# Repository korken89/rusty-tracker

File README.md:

# Rusty Tracker

**A learning board for LTE-M and tracking technologies**

## Versions

There are 2 versions of the board, based on:

1. uBlox R422-M10S
2. nRF9160 + uBlox M10S GNSS

which can be found in the `master` branch and `nrf` branch respectively.

The two IFA antennas are simulated with Ansys HFSS, files are available.

### uBlox R422-M10S version

This is the main board that development is happening for in the `firmware` folder.

The hardware is tested and working.

### nRF9160 version

This was made as well for learning, not manufactured nor tested.

## License

This work is licensed under [CERN-OHL-P](cern_ohl_p_v2.txt).

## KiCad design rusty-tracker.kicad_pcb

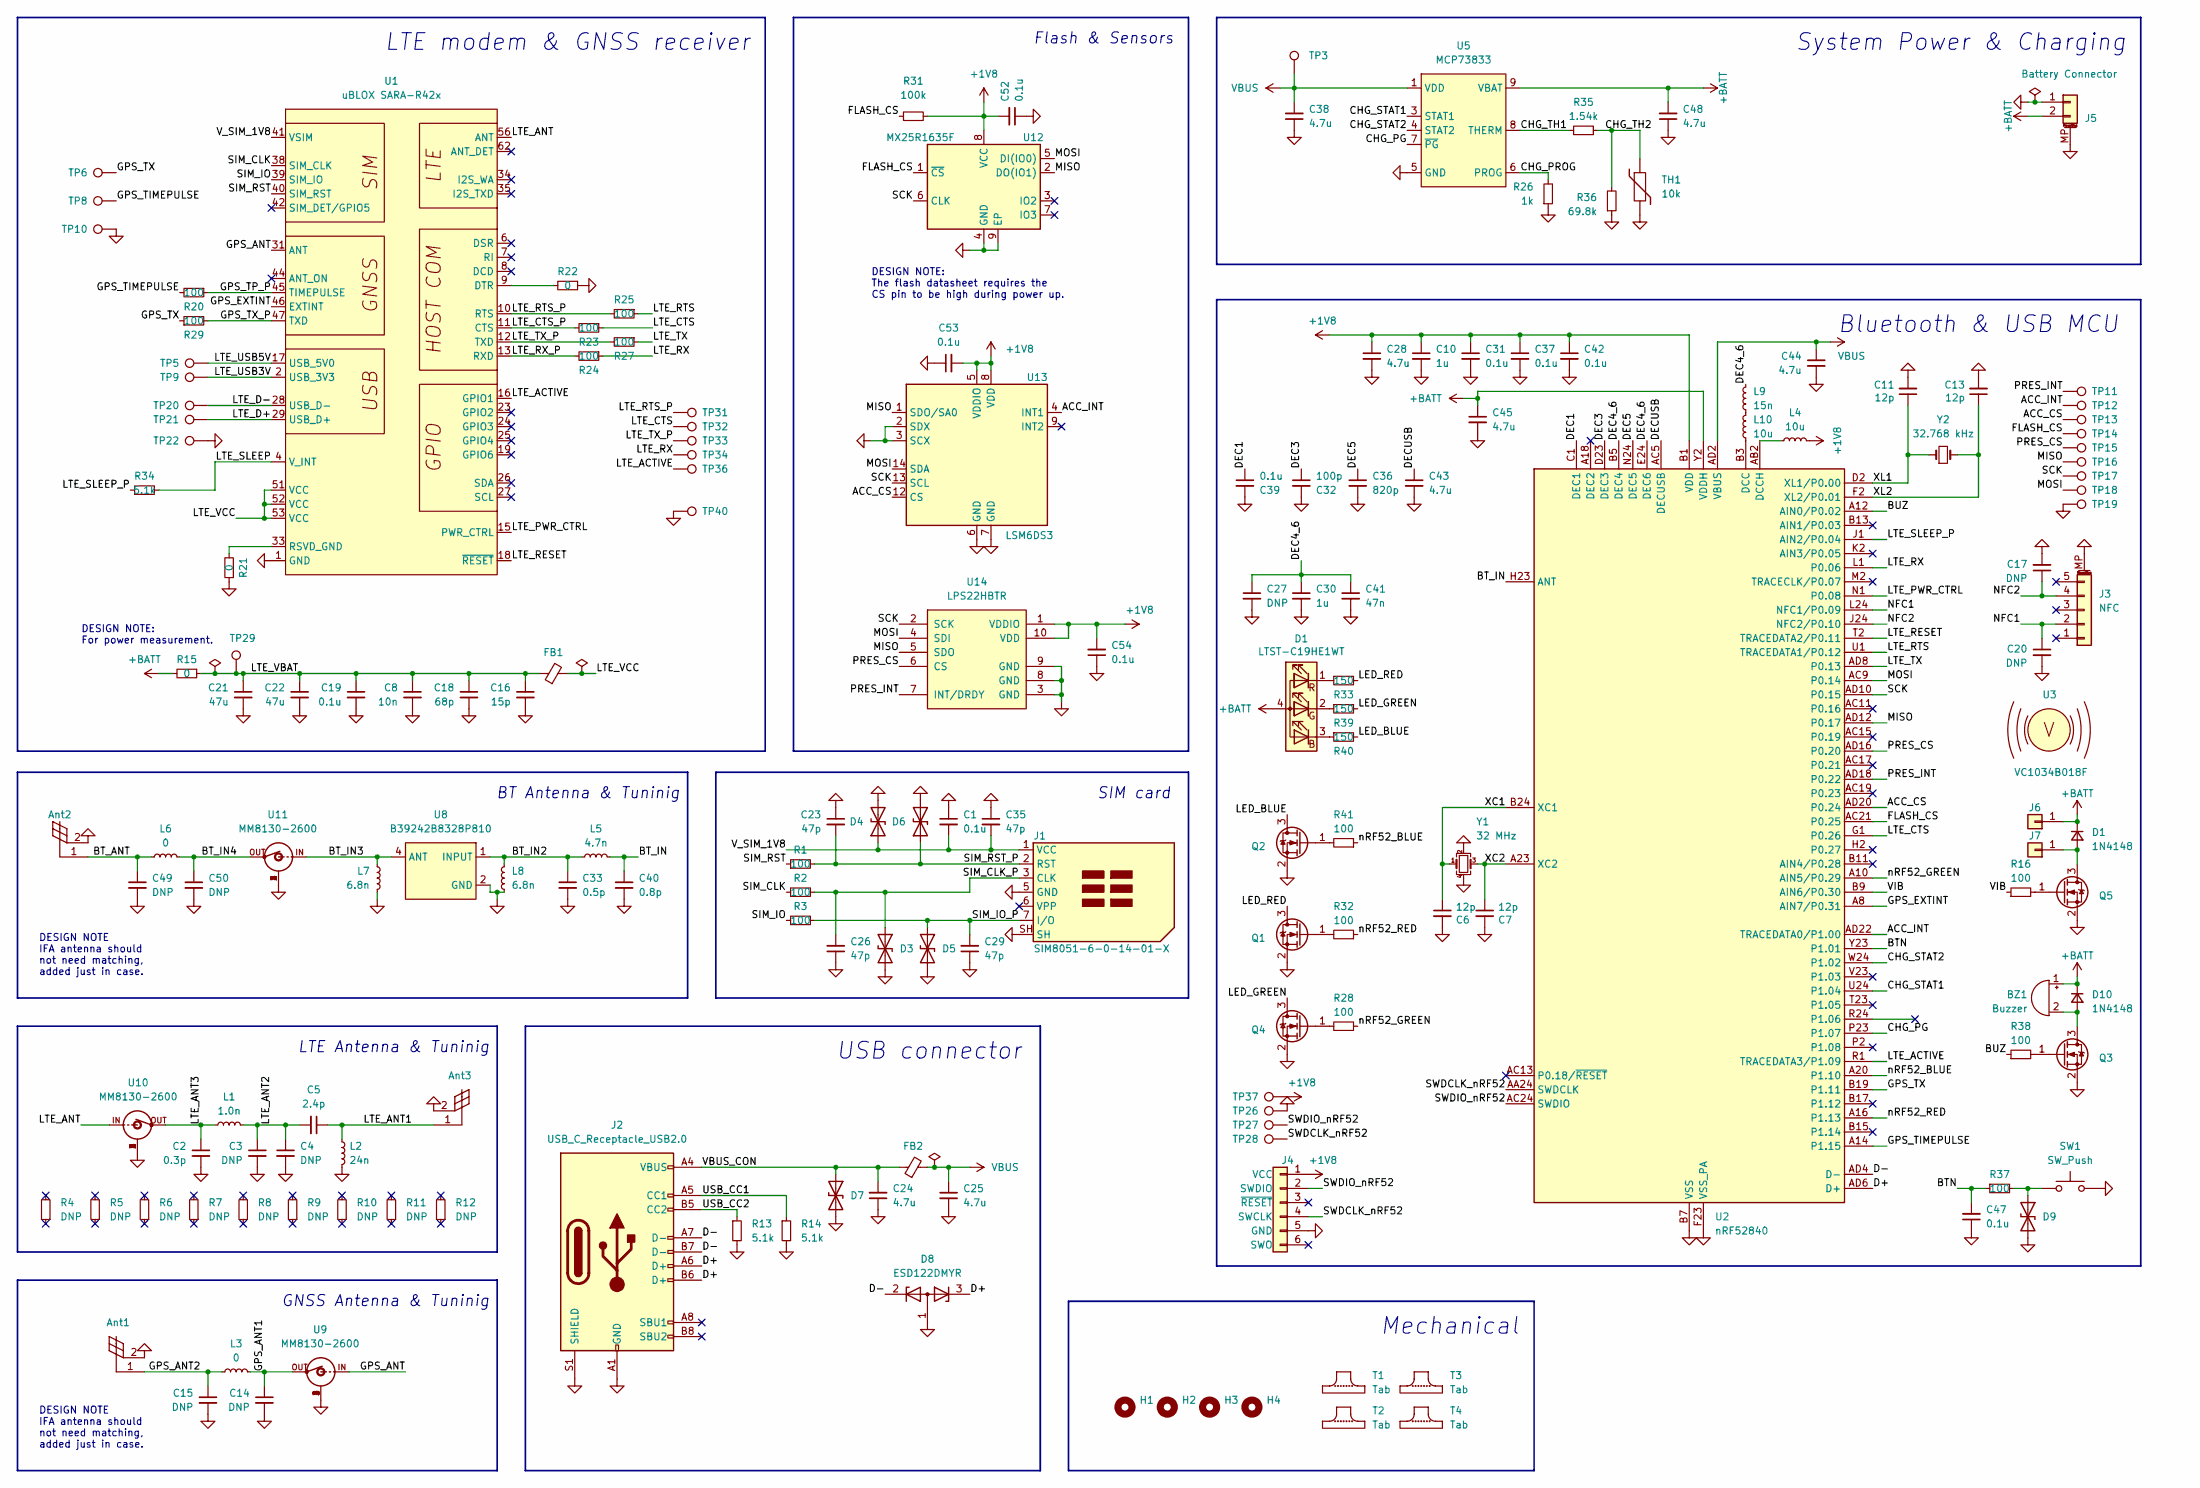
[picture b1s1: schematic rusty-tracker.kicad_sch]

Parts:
Ant1: antenna; gps-inverted-f
Ant2: antenna; 2.4ghz-inverted-f
Ant3: antenna; P822602
BZ1: Buzzer; AST0927
C1, C19, C31, C37, C39, C42, C47, C52, C53, C54: 0.1u; C_0402
C2: 0.3p; C_0402
C3, C4, C17, C20, C27: DNP; C_0402
C5: 2.4p; C_0402
C6, C7: 12p; C_0402; Tolerance 1%
C8: 10n; C_0402
C10, C30: 1u; C_0402
C11, C13: 12p; C_0402
C14, C15, C49, C50: DNP; C_0201
C16: 15p; C_0402
C18: 68p; C_0402
C21, C22: 47u; C_0805
C23, C26, C29, C35: 47p; C_0402
C24, C25, C28, C38, C43, C44, C45, C48: 4.7u; C_0402
C32: 100p; C_0402
C33: 0.5p; C_0201
C36: 820p; C_0402
C40: 0.8p; C_0201
C41: 47n; C_0402
D1, D10: 1N4148; D_0402_DFN1006
D3, D4, D5, D6, D7, D9: D_TVS; D_0402_DFN1006
D8: ESD122DMYR; X2SON
FB1, FB2: BLM18EG221SN1D; R_0603
H1, H2, H3, H4: MountingHole_Pad; MountingHole_2.2mm_M2
J1: SIM8051-6-0-14-01-X
J2: USB_C_Receptacle_USB2.0; USB_C_Receptacle_USB4105
J3: NFC; TE_0-1734839-5_1x05-1MP_P0.5mm_Horizontal
J4: tag-connect-swd; Tag-Connect_TC2030-IDC-NL_2x03_P1.27mm_Vertical
J5: Battery Connector; JST_SH_SM02B-SRSS-TB_1x02-1MP_P1.00mm_Horizontal
J6, J7: Conn_01x01; pad_circ_1.5mm
L1: 1.0n; R_0402
L2: 24n; R_0402
L3, L6: 0; R_0201
L4, L10: 10u; R_0603
L5: 4.7n; R_0201
L7, L8: 6.8n; R_0201
L9: 15n; R_0402
Q1, Q2, Q3, Q4, Q5: RUM002N02T2L; SOT-723
R1, R2, R3, R16, R20, R23, R24, R25, R27, R28, R29, R32, R37, R38, R41: 100; R_0402
R4, R5, R6, R7, R8, R9, R10, R11, R12: DNP; ANT_0402
R13, R14, R34: 5.1k; R_0402
R15, R21, R22: 0; R_0402
R26: 1k; R_0402
R31: 100k; R_0402
R33, R39, R40: 150; R_0402
R35: 1.54k; R_0402
R36: 69.8k; R_0402
SW1: SW_Push; SW_SPST_EVQP2
T1, T2, T3, T4: Tab
TH1: 10k; R_0402
TP3, TP5, TP6, TP8, TP9, TP10, TP11, TP12, TP13, TP14, TP15, TP16, TP17, TP18, TP19, TP20, TP21, TP22, TP26, TP27, TP28, TP29, TP31, TP32, TP33, TP34, TP36, TP37, TP40: TestPoint; TestPoint_Pad_D1.0mm
U1: uBLOX SARA-R42x; u-blox SARA-R4
U2: nRF52840; Nordic_AQFN-73-1EP_7x7mm_P0.5mm
U3: VC1034B018F
U5: MCP73833; DFN-10-1EP_3x3mm_P0.5mm_EP1.55x2.48mm
U8: B39242B8328P810
U9, U10, U11: MM8130-2600
U12: MX25R1635F; USON-8-3x2mm-EP
U13: LSM6DS3; LGA-14_3x2.5mm_P0.5mm_LayoutBorder3x4y
U14: LPS22HBTR; ST_HLGA-10_2x2mm_P0.5mm_LayoutBorder3x2y
Y1: 32 MHz; Crystal_4Pin_2.0x1.6mm
Y2: 32.768 kHz; Crystal_SMD_2012-2Pin_2.0x1.2mm

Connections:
+1V8: C10.1, C28.1, C31.1, C37.1, C42.1, C52.2, C53.2, C54.2, J4.1 (VCC), L4.1, R31.2, TP37.1, U2.A22 (VDD), U2.AD14 (VDD), U2.AD23 (VDD), U2.B1 (VDD), U2.W1 (VDD), U12.8 (VCC), U13.5 (VDDIO), U13.8 (VDD), U14.1 (VDDIO), U14.10 (VDD)
/ACC_CS: TP13.1, U2.AD20 (P0.24), U13.12 (CS)
/ACC_INT: TP12.1, U2.AD22 (TRACEDATA0/P1.00), U13.4 (INT1)
/BTN: C47.2, R37.1, U2.Y23 (P1.01)
/BT_ANT: Ant2.1, C49.1, L6.2
/BT_IN: C40.1, L5.1, U2.H23 (ANT)
/BT_IN2: C33.1, L5.2, L8.1, U8.1 (INPUT)
/BT_IN3: L7.2, U8.4 (ANT), U11.IN
/BT_IN4: C50.1, L6.1, U11.OUT
/BUZ: R38.1, U2.A12 (AIN0/P0.02)
/CHG_PG: U2.P23 (P1.07), U5.7 (~PG)
/CHG_PROG: R26.2, U5.6 (PROG)
/CHG_STAT1: U2.U24 (P1.04), U5.3 (STAT1)
/CHG_STAT2: U2.W24 (P1.02), U5.4 (STAT2)
/CHG_TH1: R35.2, U5.8 (THERM)
/CHG_TH2: R35.1, R36.2, TH1.1
/D+: D8.3 (K), J2.A6 (D+), J2.B6 (D+), U2.AD6 (D+)
/D-: D8.2 (K), J2.A7 (D-), J2.B7 (D-), U2.AD4 (D-)
/DEC1: C39.1, U2.C1 (DEC1)
/DEC3: C32.1, U2.D23 (DEC3)
/DEC4_6: C27.1, C30.1, C41.1, L9.1, U2.B5 (DEC4), U2.E24 (DEC6)
/DEC5: C36.1, U2.N24 (DEC5)
/DECUSB: C43.1, U2.AC5 (DECUSB)
/FLASH_CS: R31.1, TP14.1, U2.AC21 (P0.25), U12.1 (~CS)
/GPS_ANT: U1.31 (ANT), U9.IN
/GPS_ANT1: C14.1, L3.2, U9.OUT
/GPS_ANT2: Ant1.1, C15.1, L3.1
/GPS_EXTINT: U1.46 (EXTINT), U2.A8 (AIN7/P0.31)
/GPS_TIMEPULSE: R20.2, TP8.1, U2.A14 (P1.15)
/GPS_TP_P: R20.1, U1.45 (TIMEPULSE)
/GPS_TX: R29.1, TP6.1, U2.B19 (P1.11)
/GPS_TX_P: R29.2, U1.47 (TXD)
/LED_BLUE: Q2.3 (D), R40.2
/LED_GREEN: Q4.3 (D), R39.2
/LED_RED: Q1.3 (D), R33.2
/LTE_ACTIVE: TP36.1, U1.16 (GPIO1), U2.R1 (TRACEDATA3/P1.09)
/LTE_ANT: U1.56 (ANT), U10.IN
/LTE_ANT1: Ant3.1, C5.1, L2.1
/LTE_ANT2: C3.1, C4.1, C5.2, L1.2
/LTE_ANT3: C2.1, L1.1, U10.OUT
/LTE_CTS: R23.1, TP32.1, U2.G1 (P0.26)
/LTE_CTS_P: R23.2, U1.11 (CTS)
/LTE_D+: TP21.1, U1.29 (USB_D+)
/LTE_D-: TP20.1, U1.28 (USB_D-)
/LTE_PWR_CTRL: U1.15 (PWR_CTRL), U2.N1 (P0.08)
/LTE_RESET: U1.18 (~RESET), U2.T2 (TRACEDATA2/P0.11)
/LTE_RTS: R25.1, U2.U1 (TRACEDATA1/P0.12)
/LTE_RTS_P: R25.2, TP31.1, U1.10 (RTS)
/LTE_RX: R24.1, TP34.1, U2.L1 (P0.06)
/LTE_RX_P: R24.2, U1.13 (RXD)
/LTE_SLEEP: R34.2, U1.4 (V_INT)
/LTE_SLEEP_P: R34.1, U2.J1 (AIN2/P0.04)
/LTE_TX: R27.1, U2.AD8 (P0.13)
/LTE_TX_P: R27.2, TP33.1, U1.12 (TXD)
/LTE_USB3V: TP9.1, U1.2 (USB_3V3)
/LTE_USB5V: TP5.1, U1.17 (USB_5V0)
/LTE_VBAT: C8.1, C16.1, C18.1, C19.1, C21.1, C22.1, FB1.1, R15.1, TP29.1
/LTE_VCC: FB1.2, U1.51 (VCC), U1.52 (VCC), U1.53 (VCC)
/MISO: TP16.1, U2.AD12 (P0.17), U12.2 (DO(IO1)), U13.1 (SDO/SA0), U14.5 (SDO)
/MOSI: TP18.1, U2.AC9 (P0.14), U12.5 (DI(IO0)), U13.14 (SDA), U14.4 (SDI)
/NFC1: C20.1, J3.2, U2.L24 (NFC1/P0.09)
/NFC2: C17.1, J3.4, U2.J24 (NFC2/P0.10)
/PRES_CS: TP15.1, U2.AD16 (P0.20), U14.6 (CS)
/PRES_INT: TP11.1, U2.AD18 (P0.22), U14.7 (INT/DRDY)
/SCK: TP17.1, U2.AD10 (P0.15), U12.6 (CLK), U13.13 (SCL), U14.2 (SCK)
/SIM_CLK: R2.1, U1.38 (SIM_CLK)
/SIM_CLK_P: C26.2, D3.1 (A1), J1.3 (CLK), R2.2
/SIM_IO: R3.1, U1.39 (SIM_IO)
/SIM_IO_P: C29.2, D5.1 (A1), J1.7 (I/O), R3.2
/SIM_RST: R1.1, U1.40 (SIM_RST)
/SIM_RST_P: C23.2, D6.1 (A1), J1.2 (RST), R1.2
/SWDCLK_nRF52: J4.4 (SWCLK), TP28.1, U2.AA24 (SWDCLK)
/SWDIO_nRF52: J4.2 (SWDIO), TP27.1, U2.AC24 (SWDIO)
/USB_CC1: J2.A5 (CC1), R14.1
/USB_CC2: J2.B5 (CC2), R13.1
/VBUS_CON: C24.2, D7.1 (A1), FB2.1, J2.A4 (VBUS), J2.A9 (VBUS), J2.B4 (VBUS), J2.B9 (VBUS)
/VIB: R16.1, U2.B9 (AIN6/P0.30)
/V_SIM_1V8: C1.2, C35.2, D4.1 (A1), J1.1 (VCC), U1.41 (VSIM)
/XC1: C6.1, U2.B24 (XC1), Y1.1
/XC2: C7.1, U2.A23 (XC2), Y1.3
/XL1: C11.1, U2.D2 (XL1/P0.00), Y2.1
/XL2: C13.1, U2.F2 (XL2/P0.01), Y2.2
/nRF52_BLUE: R41.1, U2.A20 (P1.10)
/nRF52_GREEN: R28.1, U2.A10 (AIN5/P0.29)
/nRF52_RED: R32.1, U2.A16 (P1.13)
GND: Ant1.2, Ant2.2, Ant3.2, C1.1, C2.2, C3.2, C4.2, C6.2, C7.2, C8.2, C10.2, C11.2, C13.2, C14.2, C15.2, C16.2, C17.2, C18.2, C19.2, C20.2, C21.2, C22.2, C23.1, C24.1, C25.2, C26.1, C27.2, C28.2, C29.1, C30.2, C31.2, C32.2, C33.2, C35.1, C36.2, C37.2, C38.1, C39.2, C40.2, C41.2, C42.2, C43.2, C44.2, C45.2, C47.1, C48.1, C49.2, C50.2, C52.1, C53.1, C54.1, D3.2 (A2), D4.2 (A2), D5.2 (A2), D6.2 (A2), D7.2 (A2), D8.1 (A), D9.2 (A2), J1.5 (GND), J1.SH, J2.A1 (GND), J2.A12 (GND), J2.B1 (GND), J2.B12 (GND), J2.S1 (SHIELD), J3.MP (MountPin), J4.5 (GND), J5.1, J5.MP (MountPin), L2.2, L7.1, L8.2, Q1.2 (S), Q2.2 (S), Q3.2 (S), Q4.2 (S), Q5.2 (S), R13.2, R14.2, R21.1, R22.1, R26.1, R36.1, SW1.2, TH1.2, TP10.1, TP19.1, TP22.1, TP26.1, TP40.1, U1.1 (GND), U1.3 (GND), U1.5 (GND), U1.14 (GND), U1.20 (GND), U1.21 (GND), U1.22 (GND), U1.30 (GND), U1.32 (GND), U1.43 (GND), U1.50 (GND), U1.54 (GND), U1.55 (GND), U1.57 (GND), U1.58 (GND), U1.59 (GND), U1.60 (GND), U1.61 (GND), U1.63 (GND), U1.64 (GND), U1.65 (GND), U1.66 (GND), U1.67 (GND), U1.68 (GND), U1.69 (GND), U1.70 (GND), U1.71 (GND), U1.72 (GND), U1.73 (GND), U1.74 (GND), U1.75 (GND), U1.76 (GND), U1.77 (GND), U1.78 (GND), U1.79 (GND), U1.80 (GND), U1.81 (GND), U1.82 (GND), U1.83 (GND), U1.84 (GND), U1.85 (GND), U1.86 (GND), U1.87 (GND), U1.88 (GND), U1.89 (GND), U1.90 (GND), U1.91 (GND), U1.92 (GND), U1.93 (GND), U1.94 (GND), U1.95 (GND), U1.96 (GND), U2.B7 (VSS), U2.EP (VSS), U2.F23 (VSS_PA), U5.5 (GND), U5.11 (PAD), U8.2 (GND), U8.3 (GND), U8.5 (GND), U9.1, U9.2, U9.3, U9.4, U10.1, U10.2, U10.3, U10.4, U11.1, U11.2, U11.3, U11.4, U12.4 (GND), U12.9 (EP), U13.2 (SDX), U13.3 (SCX), U13.6 (GND), U13.7 (GND), U14.3 (GND), U14.8 (GND), U14.9 (GND), Y1.2, Y1.4
unnamed: BZ1.2 (+), D10.2 (A), Q3.3 (D)
unnamed: D9.1 (A1), R37.2, SW1.1
unnamed: L9.2, L10.1
unnamed: Q1.1 (G), R32.2
unnamed: Q2.1 (G), R41.2
unnamed: Q3.1 (G), R38.2
unnamed: Q4.1 (G), R28.2
unnamed: Q5.1 (G), R16.2
unnamed: R22.2, U1.9 (DTR)
unnamed: R21.2, U1.33 (RSVD_GND)
unnamed: L10.2, U2.B3 (DCC)
unnamed: L4.2, U2.AB2 (DCCH)
VBUS: C25.1, C38.2, C44.1, FB2.2, TP3.1, U2.AD2 (VBUS), U5.1 (VDD), U5.2 (VDD)

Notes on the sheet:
DESIGN NOTE IFA antenna should not need matching, added just in case.
GNSS Antenna & Tuninig
System Power & Charging
LTE modem & GNSS receiver
SIM card
LTE Antenna & Tuninig
DESIGN NOTE: The flash datasheet requires the CS pin to be high during power up.
BT Antenna & Tuninig
DESIGN NOTE: For power measurement.
Bluetooth & USB MCU
USB connector
Mechanical
Flash & Sensors

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
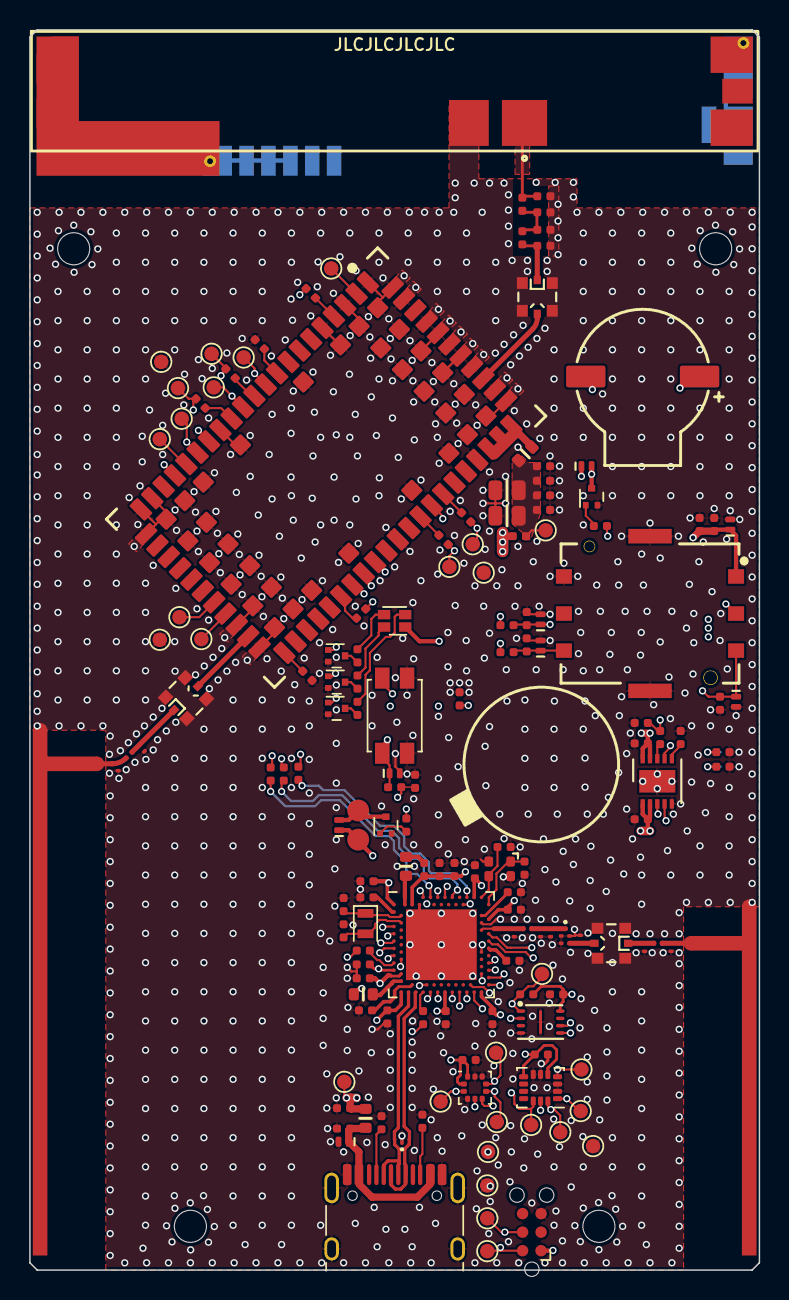
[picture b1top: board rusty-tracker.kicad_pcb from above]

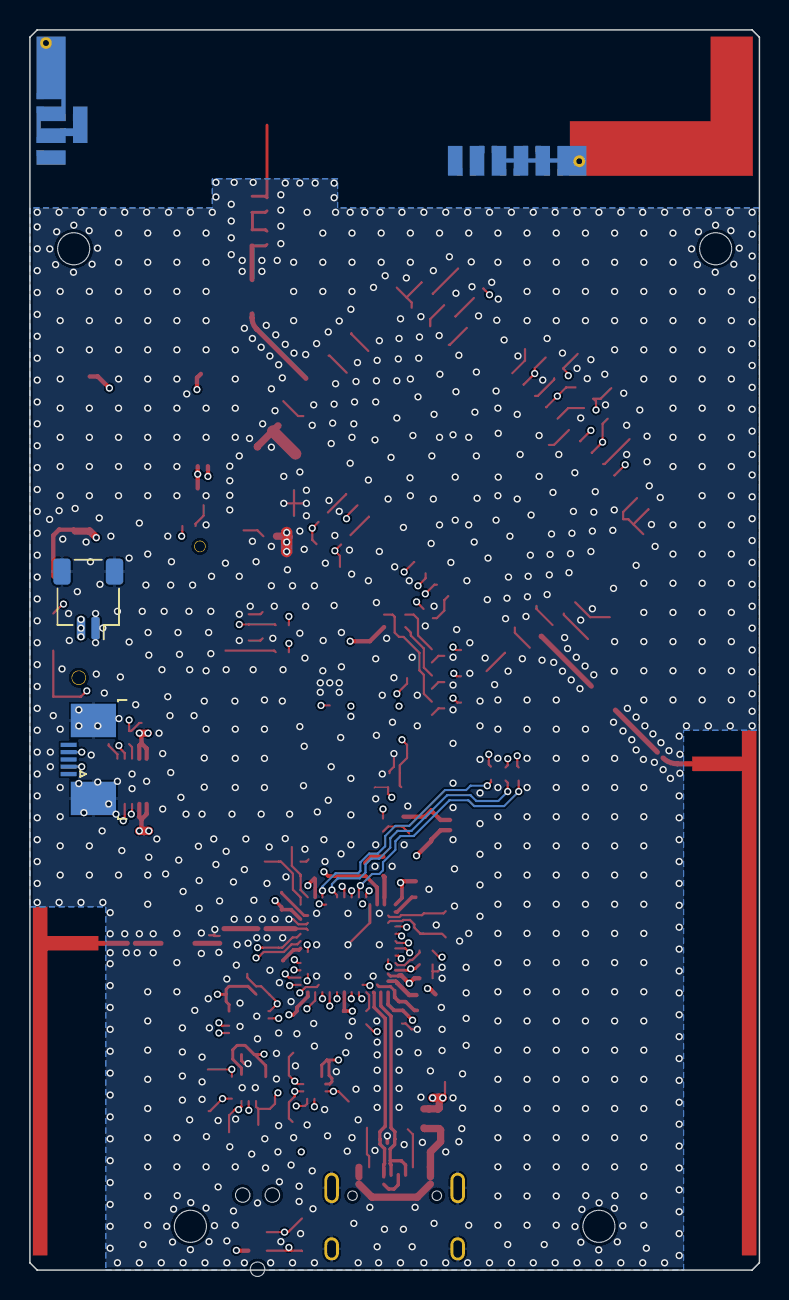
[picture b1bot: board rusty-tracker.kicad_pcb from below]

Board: 6 copper layers, 50.0 x 85.0 mm, 181 parts (12 on the bottom side), 104 nets.

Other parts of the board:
D2: LTST-C19HE1WT; LED_LiteOn_LTST-C19HE1WT
kibuzzard-63E4FB2E: G***; kibuzzard-63E4FB2E
kibuzzard-63E4FB20: G***; kibuzzard-63E4FB20
kibuzzard-63E50121: G***; kibuzzard-63E50121
kibuzzard-63FA6CC8: G***; kibuzzard-63FA6CC8
kibuzzard-63FA0532: G***; kibuzzard-63FA0532

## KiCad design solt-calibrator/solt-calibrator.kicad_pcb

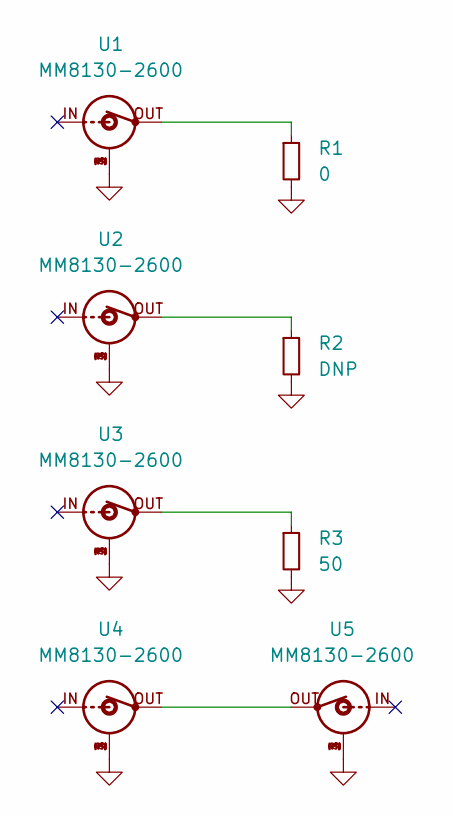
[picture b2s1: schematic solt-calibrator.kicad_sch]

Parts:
R1: 0; R_0603_1608Metric
R2: DNP; R_0603_1608Metric
R3: 50; R_0603_1608Metric
U1, U2, U3, U4, U5: MM8130-2600

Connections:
GND: R1.2, R2.2, R3.2, U1.1, U1.2, U1.3, U1.4, U2.1, U2.2, U2.3, U2.4, U3.1, U3.2, U3.3, U3.4, U4.1, U4.2, U4.3, U4.4, U5.1, U5.2, U5.3, U5.4
unnamed: R1.1, U1.OUT
unnamed: R2.1, U2.OUT
unnamed: R3.1, U3.OUT
unnamed: U4.OUT, U5.OUT

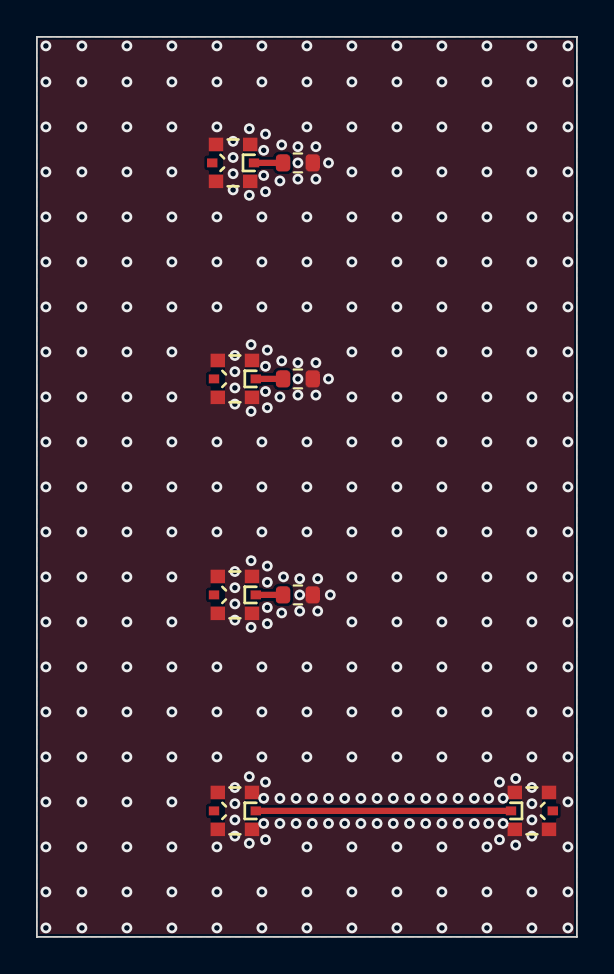
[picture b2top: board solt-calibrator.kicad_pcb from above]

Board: 4 copper layers, 30.0 x 50.0 mm, 8 parts (0 on the bottom side), 5 nets.

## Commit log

2023-02-27 Rusty Tracker - nRF9160 version
2023-02-27 Add README
2023-02-27 Rusty Tracker - uBlox version
2023-02-27 Add support for VBAT -> VDDH, and DCDC for the nRF52840
2023-02-28 Add protection & debounce to button
2023-03-01 Make LDO DNP
2023-03-02 Remove GND connection in screws
2023-03-02 Fix antenna feed and ground
2023-03-12 KiCAD v7, 6 layer version
2023-03-15 Added buzzer
2023-03-17 Firmware skeleton
2023-03-17 Systick working
2023-03-19 Fix swapped thermistor resistors
2023-03-19 Update runner to kicad 7
2023-03-19 Update ADC resistor divider values
2023-03-19 Testing LEDs and ADC
2023-03-21 Use internal VDDH measurement
2023-03-22 Updated with buzzer and vibrator, removed voltage dividers
    As they are available in the nRF52840 and charging IC
2023-03-22 Update to v7 CI
2023-03-22 Order sent to JLCPCB
2023-03-25 Nicer text
2023-03-26 Update via to 0.3/0.5 mm to work with new JLCPCB 6L service without extra cost
2023-03-26 Moved firmware to master, added charge status and more LED control
2023-04-02 Add an exported schematic so people don't need to download and check
2023-04-03 Testing embassy HAL
2023-04-04 MFPNs added
2023-04-07 More HAL testing
2023-04-07 More impl
2023-04-08 Testing some connectivity
2023-04-09 TCP working
2023-04-11 Starting modem abstraction
2023-04-12 Add a modem log for devving
2023-04-14 Update licenses
2023-04-22 Move to branch, save work
2023-04-22 Started cmd
2023-04-22 Init code added, but not parsing
2023-04-22 Parse system info
2023-04-22 Fix typos
2023-04-22 Cleaning, add todo for config
2023-04-22 Simplify stripping of whitespace
2023-04-23 Improve logging and error handling
2023-04-23 More thoughs on the RX/TX worker and their parsing
2023-04-23 Robustifying thoughts for parsing reponses
2023-04-23 Update RX buffer size, band scan can overflow
2023-04-23 Move everything to bsp and tasks again
2023-04-23 Fix delay in PWM setting, fade from red to green for battery voltage
2023-04-23 Almost got modem init building
2023-04-24 Testing battery
2023-04-25 Modem initializes successfully
2023-04-25 Make printing better, add socket closing on startup
2023-04-27 Start implementing cmd/resp
2023-05-01 Better buffers
2023-05-01 Save
2023-05-01 First command almost working
2023-05-02 DNS works
2023-05-03 Testing more
2023-06-18 Testing nlsp-settings
